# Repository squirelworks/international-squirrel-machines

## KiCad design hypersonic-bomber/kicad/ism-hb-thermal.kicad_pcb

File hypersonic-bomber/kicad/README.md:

# ISM Hypersonic Bomber — KiCad (thermal / TPS sense) (#37)

Study-scale **educational thermal / TPS instrumentation** board for ISM-HB-1. Open with **KiCad 8**.

## Out of scope (hard)

- **No** weapons, munitions, guidance, seekers, warheads, fuzing, or arming
- **No** operational employment or targeting
- **No** scramjet / propulsion design recipes
- **No** ITAR/EAR TPS formulations or classified materials data
- Channels are **teaching sense / status stubs** only

## Project-local libraries

| File | Role |
|------|------|
| `sym-lib-table` | `ISM.kicad_sym` |
| `fp-lib-table` | `ISM.pretty/` |
| `ISM.kicad_sym` / `ISM.pretty/` | Study MCU, IMU, RADIO, CONN |

## Schematic / PCB (`ism-hb-thermal`)

| Net / header | Role |
|--------------|------|
| I2C | IMU / cabin / skin sensors stub |
| SPI | Telemetry / flash stub |
| J1 `ADC_TC1` | Thermocouple / RTD sense stub |
| J2 `ADC_TC2` | Second thermal sense stub |
| J3 `GPIO_TPS_OK` | TPS health status stub |
| J4 `GPIO_OVERTEMP` | Over-temp inhibit packaging stub |
| 3V3 / 5V / GND | Rails with PWR_FLAG |

Study MCU footprint pitch is packaging-level (not production RP2040 0.4 mm).

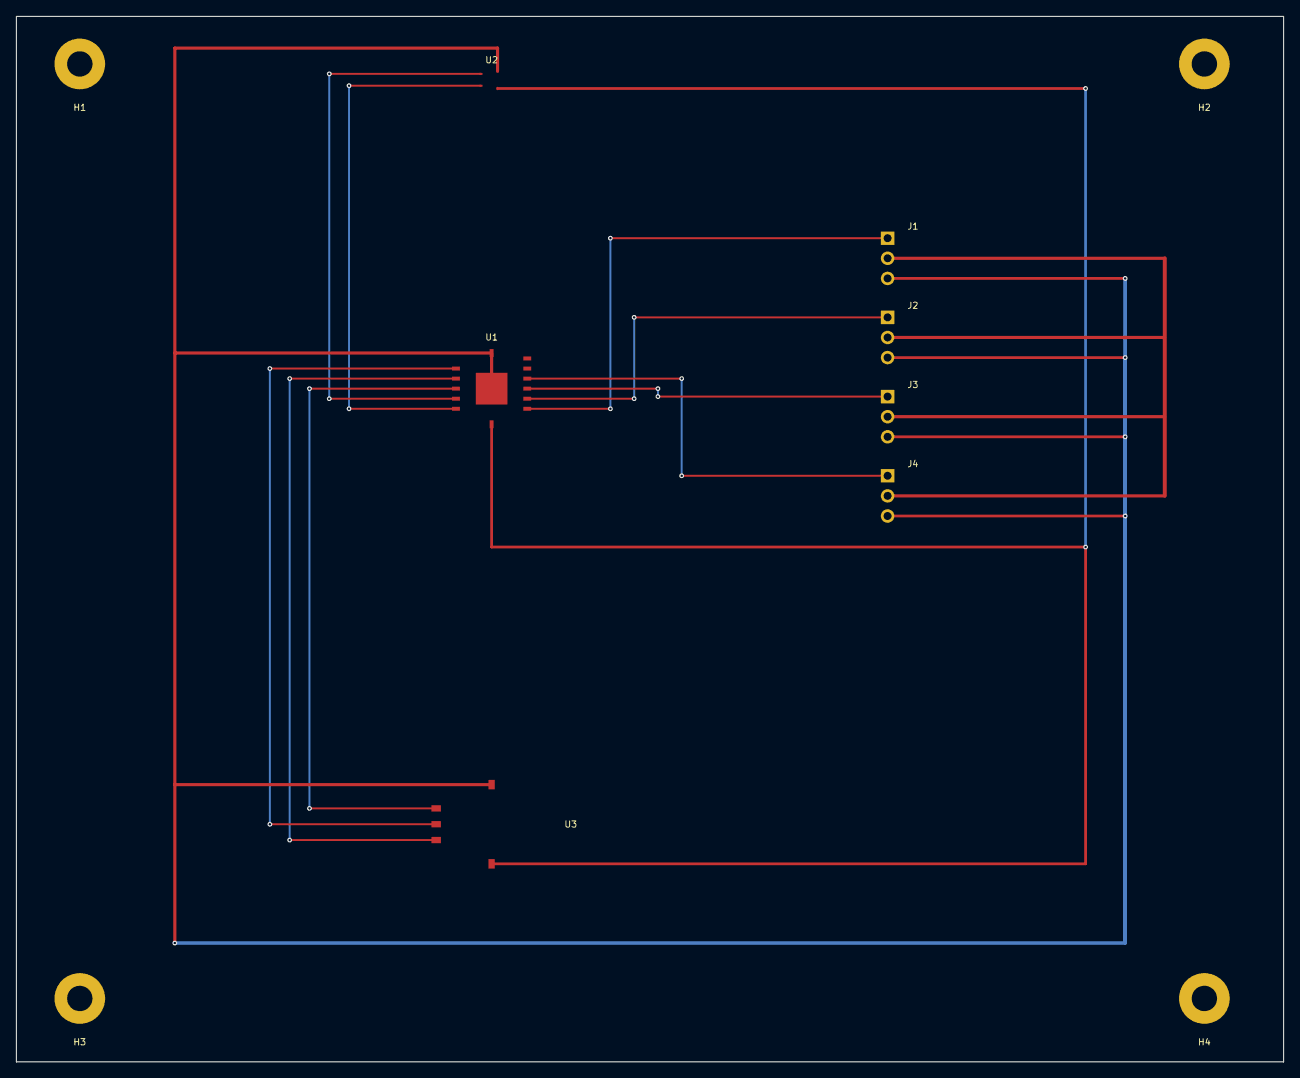
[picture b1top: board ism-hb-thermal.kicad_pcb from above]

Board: 2 copper layers, 160.0 x 132.0 mm, 11 parts (0 on the bottom side), 12 nets.

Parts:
H1, H2, H3, H4: M3; MountingHole_3.2mm_M3
J1: J1; PinHeader_1x03_P2.54mm
J2: J2; PinHeader_1x03_P2.54mm
J3: J3; PinHeader_1x03_P2.54mm
J4: J4; PinHeader_1x03_P2.54mm
U1: RP2040; QFN-56-1EP_7x7mm_P0.4mm
U2: IMU; LGA-14_3x2.5mm_P0.5mm
U3: RADIO; RADIO_Module

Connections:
3V3: U1.11, U2.4, U3.5
5V: J1.2, J2.2, J3.2, J4.2
ADC_TC1: J1.1, U1.6
ADC_TC2: J2.1, U1.7
GND: J1.3, J2.3, J3.3, J4.3, U1.10, U1.EP, U2.3, U3.4
GPIO_OVERTEMP: J4.1, U1.9
GPIO_TPS_OK: J3.1, U1.8
I2C_SCL: U1.2, U2.2
I2C_SDA: U1.1, U2.1
SPI_MISO: U1.5, U3.2
SPI_MOSI: U1.4, U3.1
SPI_SCK: U1.3, U3.3

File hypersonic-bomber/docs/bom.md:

# Hypersonic bomber — educational master BOM (#37)

**Product:** ISM-HB-1  
**Slice:** study BOM tying the thermal/TPS-sense fab package to the blunt-cone STL / structural stubs.

## Out of scope (hard)

- Weapons, munitions, guidance, seekers, warheads, fuzing, or arming
- Operational employment, targeting, or mission planning
- Scramjet / propulsion **design recipes** or performance prediction
- Export-controlled (ITAR/EAR) TPS formulations or classified materials data
- **Not** a procurement order — PNs freeze at inquire-for-release

## Board (SMT) — from `../fab/BOM.csv`

| Ref | Qty | Value | Role |
|-----|-----|-------|------|
| U1 | 1 | RP2040 | Thermal / TPS sense MCU stub |
| U2 | 1 | IMU | Attitude stub |
| U3 | 1 | RADIO | Telemetry stub |
| J1 | 1 | PinHeader 1×03 | TPS thermistor / TC sense stub |
| J2 | 1 | PinHeader 1×03 | Heat-flux sense stub |
| J3 | 1 | PinHeader 1×03 | TPS health / spare thermal stub |
| J4 | 1 | PinHeader 1×03 | Over-temp packaging stub |
| H1–H4 | 4 | M3 hole | Board mounting |

## Mechanical / study article

| ID | Qty | Item | Source |
|----|-----|------|--------|
| MECH-CONE-STL | 1 | `blunt_cone_study.stl` print (blunt cone + TPS shell ghosts) | `../mechanical/` |
| MECH-SCAD | 1 | `blunt_cone_study.scad` parametric source | `../shell/` |
| MECH-FAST-M3 | lot | M3 hardware for thermal board tray | study |
| MECH-TRAY | 1 | Thermal-board tray stub under TPS shell | `structural.yaml` |
| TPS-CLASS | ref | Textbook TPS class coupon placeholders | `heat-shield-tps.md` — open literature classes only |

## Electrical harness (study)

| ID | Qty | Item | Notes |
|----|-----|------|-------|
| HAR-TC1 | 1 | Sense lead | J1 teaching thermistor/TC stub |
| HAR-FLUX | 1 | Sense lead | J2 heat-flux stub |
| HAR-TPS | 1 | Status lead | J3 TPS_OK packaging stub |
| HAR-OT | 1 | Status lead | J4 over-temp packaging stub — not a weapon inhibit |
| HAR-PWR | 1 | 5 V / GND stub lead | Bench supply only |

## Out of BOM (explicit)

Weapons, seekers, guidance, munition propulsion, warheads, fuzing/arming, classified TPS recipes, scramjet design kits.

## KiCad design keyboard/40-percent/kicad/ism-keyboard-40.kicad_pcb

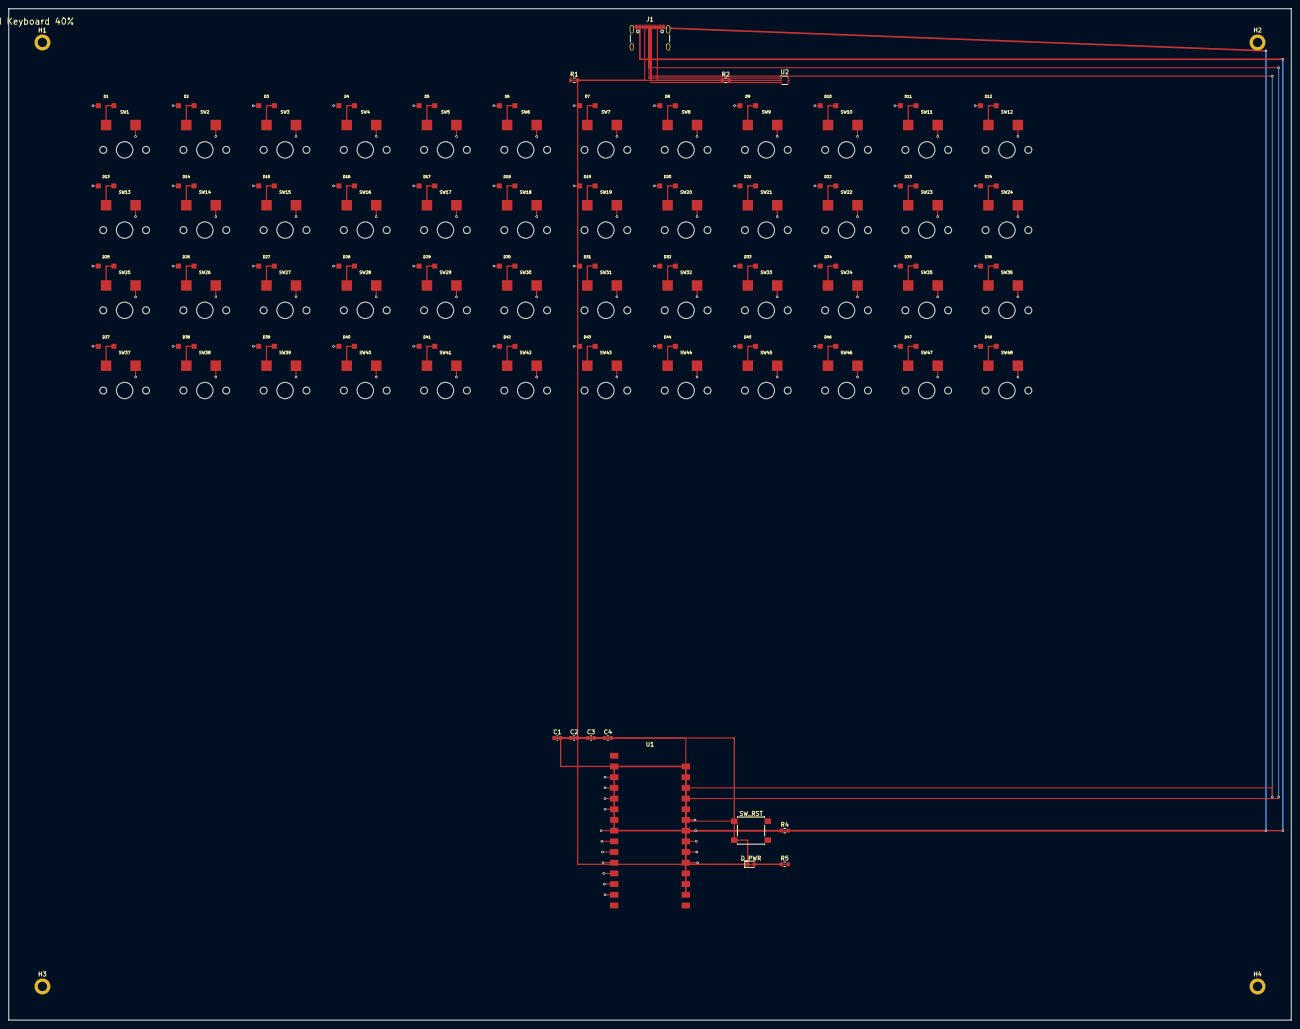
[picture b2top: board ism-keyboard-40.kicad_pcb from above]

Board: 4 copper layers, 304.6 x 240.2 mm, 113 parts (0 on the bottom side), 73 nets.

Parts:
C1, C2, C3, C4: 100nF; C_0603_1608Metric
D1, D2, D3, D4, D5, D6, D7, D8, D9, D10, D11, D12, D13, D14, D15, D16, D17, D18, D19, D20, D21, D22, D23, D24, D25, D26, D27, D28, D29, D30, D31, D32, D33, D34, D35, D36, D37, D38, D39, D40, D41, D42, D43, D44, D45, D46, D47, D48: 1N4148W; D_SOD123_nocrt
D_PWR: LED; LED_0603_1608Metric
H1, H2, H3, H4: M2; MountingHole_2.2mm_M2_DIN965_Pad
J1: USB_C; USB_C_Receptacle_GCT_USB4105-xx-A_16P_TopMnt_Horizontal
R1, R2: 5.1k; R_0603_1608Metric
R4: 10k; R_0603_1608Metric
R5: 1k; R_0603_1608Metric
SW1: ESC; SW_MX_Hotswap
SW2: Q; SW_MX_Hotswap
SW3: W; SW_MX_Hotswap
SW4: E; SW_MX_Hotswap
SW5: R; SW_MX_Hotswap
SW6: T; SW_MX_Hotswap
SW7: Y; SW_MX_Hotswap
SW8: U; SW_MX_Hotswap
SW9: I; SW_MX_Hotswap
SW10: O; SW_MX_Hotswap
SW11: P; SW_MX_Hotswap
SW12: BSPC; SW_MX_Hotswap
SW13: TAB; SW_MX_Hotswap
SW14: A; SW_MX_Hotswap
SW15: S; SW_MX_Hotswap
SW16: D; SW_MX_Hotswap
SW17: F; SW_MX_Hotswap
SW18: G; SW_MX_Hotswap
SW19: H; SW_MX_Hotswap
SW20: J; SW_MX_Hotswap
SW21: K; SW_MX_Hotswap
SW22: L; SW_MX_Hotswap
SW23: SCLN; SW_MX_Hotswap
SW24: ENT; SW_MX_Hotswap
SW25: LSFT; SW_MX_Hotswap
SW26: Z; SW_MX_Hotswap
SW27: X; SW_MX_Hotswap
SW28: C; SW_MX_Hotswap
SW29: V; SW_MX_Hotswap
SW30: B; SW_MX_Hotswap
SW31: N; SW_MX_Hotswap
SW32: M; SW_MX_Hotswap
SW33: COMM; SW_MX_Hotswap
SW34: DOT; SW_MX_Hotswap
SW35: SLSH; SW_MX_Hotswap
SW36: RSFT; SW_MX_Hotswap
SW37: LCTL; SW_MX_Hotswap
SW38: LGUI; SW_MX_Hotswap
SW39: LALT; SW_MX_Hotswap
SW40: FN; SW_MX_Hotswap
SW41: SPC; SW_MX_Hotswap
SW42: SPC2; SW_MX_Hotswap
SW43: SPC3; SW_MX_Hotswap
SW44: RALT; SW_MX_Hotswap
SW45: LEFT; SW_MX_Hotswap
SW46: DOWN; SW_MX_Hotswap
SW47: UP; SW_MX_Hotswap
SW48: RIGHT; SW_MX_Hotswap
SW_RST: RESET; SW_SPST_PTS645
U1: RP2040_MOD; ISM_RP2040_Module
U2: USBLC6-2SC6; SOT-666

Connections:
+3V3: C1.1, C2.1, C3.1, C4.1, R4.2, R5.1, U1.14
+5V: J1.A4, J1.A9, J1.B4, J1.B9, U1.15, U2.5
CC1: J1.A5, R1.1
CC2: J1.B5, R2.1
COL0: D1.1, D13.1, D25.1, D37.1, U1.7
COL1: D2.1, D14.1, D26.1, D38.1, U1.8
COL2: D3.1, D15.1, D27.1, D39.1, U1.9
COL3: D4.1, D16.1, D28.1, D40.1, U1.10
COL4: D5.1, D17.1, D29.1, D41.1, U1.11
COL5: D6.1, D18.1, D30.1, D42.1, U1.12
COL6: D7.1, D19.1, D31.1, D43.1, U1.13
COL7: D8.1, D20.1, D32.1, D44.1, U1.19
COL8: D9.1, D21.1, D33.1, D45.1, U1.20
COL9: D10.1, D22.1, D34.1, D46.1, U1.21
COL10: D11.1, D23.1, D35.1, D47.1, U1.22
COL11: D12.1, D24.1, D36.1, D48.1, U1.23
GND: C1.2, C2.2, C3.2, C4.2, D_PWR.1, J1.A1, J1.A8, J1.A12, J1.B1, J1.B8, J1.B12, J1.S1, R1.2, R2.2, SW_RST.2, U1.1, U1.26, U2.2
LED_A: D_PWR.2, R5.2
NET_SW1: D1.2, SW1.2
NET_SW2: D2.2, SW2.2
NET_SW3: D3.2, SW3.2
NET_SW4: D4.2, SW4.2
NET_SW5: D5.2, SW5.2
NET_SW6: D6.2, SW6.2
NET_SW7: D7.2, SW7.2
NET_SW8: D8.2, SW8.2
NET_SW9: D9.2, SW9.2
NET_SW10: D10.2, SW10.2
NET_SW11: D11.2, SW11.2
NET_SW12: D12.2, SW12.2
NET_SW13: D13.2, SW13.2
NET_SW14: D14.2, SW14.2
NET_SW15: D15.2, SW15.2
NET_SW16: D16.2, SW16.2
NET_SW17: D17.2, SW17.2
NET_SW18: D18.2, SW18.2
NET_SW19: D19.2, SW19.2
NET_SW20: D20.2, SW20.2
NET_SW21: D21.2, SW21.2
NET_SW22: D22.2, SW22.2
NET_SW23: D23.2, SW23.2
NET_SW24: D24.2, SW24.2
NET_SW25: D25.2, SW25.2
NET_SW26: D26.2, SW26.2
NET_SW27: D27.2, SW27.2
NET_SW28: D28.2, SW28.2
NET_SW29: D29.2, SW29.2
NET_SW30: D30.2, SW30.2
NET_SW31: D31.2, SW31.2
NET_SW32: D32.2, SW32.2
NET_SW33: D33.2, SW33.2
NET_SW34: D34.2, SW34.2
NET_SW35: D35.2, SW35.2
NET_SW36: D36.2, SW36.2
NET_SW37: D37.2, SW37.2
NET_SW38: D38.2, SW38.2
NET_SW39: D39.2, SW39.2
NET_SW40: D40.2, SW40.2
NET_SW41: D41.2, SW41.2
NET_SW42: D42.2, SW42.2
NET_SW43: D43.2, SW43.2
NET_SW44: D44.2, SW44.2
NET_SW45: D45.2, SW45.2
NET_SW46: D46.2, SW46.2
NET_SW47: D47.2, SW47.2
NET_SW48: D48.2, SW48.2
ROW0: SW1.1, SW2.1, SW3.1, SW4.1, SW5.1, SW6.1, SW7.1, SW8.1, SW9.1, SW10.1, SW11.1, SW12.1, U1.2
ROW1: SW13.1, SW14.1, SW15.1, SW16.1, SW17.1, SW18.1, SW19.1, SW20.1, SW21.1, SW22.1, SW23.1, SW24.1, U1.3
ROW2: SW25.1, SW26.1, SW27.1, SW28.1, SW29.1, SW30.1, SW31.1, SW32.1, SW33.1, SW34.1, SW35.1, SW36.1, U1.4
ROW3: SW37.1, SW38.1, SW39.1, SW40.1, SW41.1, SW42.1, SW43.1, SW44.1, SW45.1, SW46.1, SW47.1, SW48.1, U1.5
RUN: R4.1, SW_RST.1, U1.18
USB_DM: J1.A7, J1.B7, U1.16, U2.3, U2.4
USB_DP: J1.A6, J1.B6, U1.17, U2.1, U2.6

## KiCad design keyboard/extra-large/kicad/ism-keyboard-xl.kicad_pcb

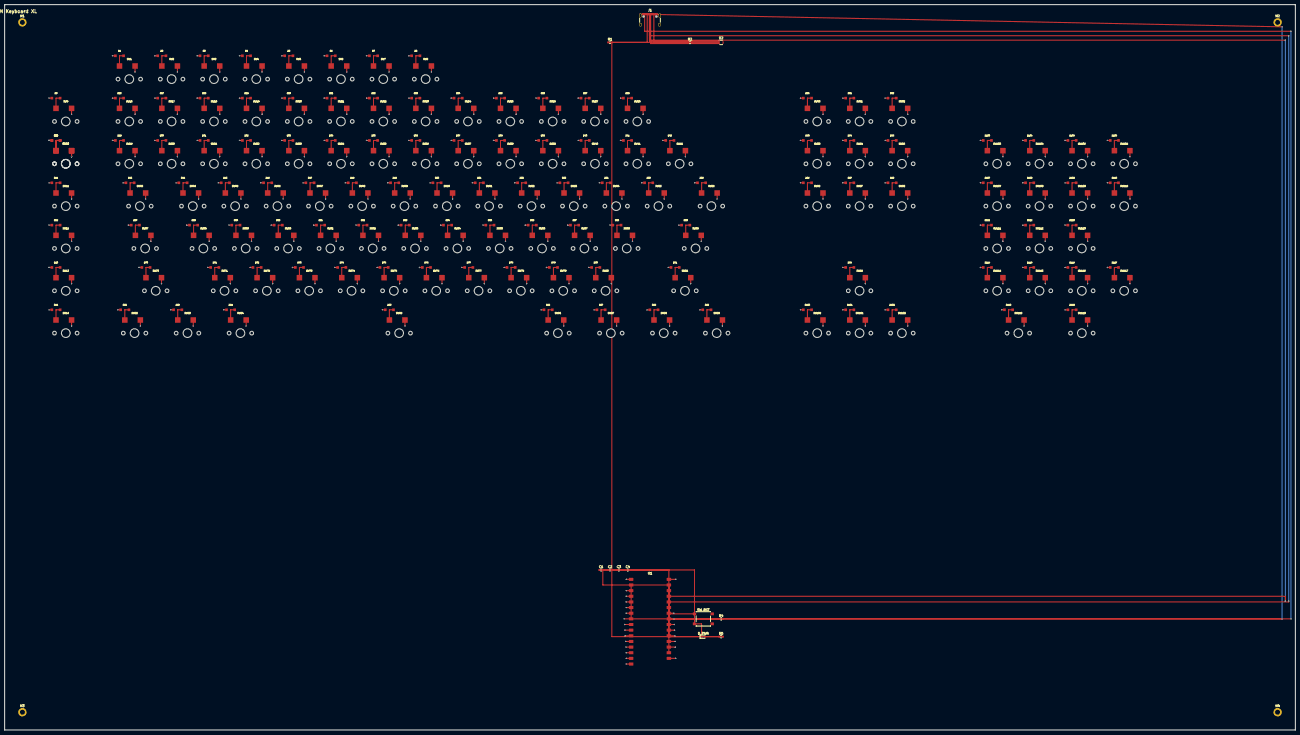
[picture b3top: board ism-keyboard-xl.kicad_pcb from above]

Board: 4 copper layers, 580.8 x 326.4 mm, 255 parts (0 on the bottom side), 152 nets.

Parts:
C1, C2, C3, C4: 100nF; C_0603_1608Metric
D1, D2, D3, D4, D5, D6, D7, D8, D9, D10, D11, D12, D13, D14, D15, D16, D17, D18, D19, D20, D21, D22, D23, D24, D25, D26, D27, D28, D29, D30, D31, D32, D33, D34, D35, D36, D37, D38, D39, D40, D41, D42, D43, D44, D45, D46, D47, D48, D49, D50, D51, D52, D53, D54, D55, D56, D57, D58, D59, D60, D61, D62, D63, D64, D65, D66, D67, D68, D69, D70, D71, D72, D73, D74, D75, D76, D77, D78, D79, D80, D81, D82, D83, D84, D85, D86, D87, D88, D89, D90, D91, D92, D93, D94, D95, D96, D97, D98, D99, D100, D101, D102, D103, D104, D105, D106, D107, D108, D109, D110, D111, D112, D113, D114, D115, D116, D117, D118, D119: 1N4148W; D_SOD123_nocrt
D_PWR: LED; LED_0603_1608Metric
H1, H2, H3, H4: M2; MountingHole_2.2mm_M2_DIN965_Pad
J1: USB_C; USB_C_Receptacle_GCT_USB4105-xx-A_16P_TopMnt_Horizontal
R1, R2: 5.1k; R_0603_1608Metric
R4: 10k; R_0603_1608Metric
R5: 1k; R_0603_1608Metric
SW1: VOLD; SW_MX_Hotswap
SW2: VOLU; SW_MX_Hotswap
SW3: MUTE; SW_MX_Hotswap
SW4: PREV; SW_MX_Hotswap
SW5: PLAY; SW_MX_Hotswap
SW6: NEXT; SW_MX_Hotswap
SW7: STOP; SW_MX_Hotswap
SW8: CALC; SW_MX_Hotswap
SW9: M1; SW_MX_Hotswap
SW10: M2; SW_MX_Hotswap
SW11: M3; SW_MX_Hotswap
SW12: M4; SW_MX_Hotswap
SW13: M5; SW_MX_Hotswap
SW14: M6; SW_MX_Hotswap
SW15: M7; SW_MX_Hotswap
SW16: ESC; SW_MX_Hotswap
SW17: F1; SW_MX_Hotswap
SW18: F2; SW_MX_Hotswap
SW19: F3; SW_MX_Hotswap
SW20: F4; SW_MX_Hotswap
SW21: F5; SW_MX_Hotswap
SW22: F6; SW_MX_Hotswap
SW23: F7; SW_MX_Hotswap
SW24: F8; SW_MX_Hotswap
SW25: F9; SW_MX_Hotswap
SW26: F10; SW_MX_Hotswap
SW27: F11; SW_MX_Hotswap
SW28: F12; SW_MX_Hotswap
SW29: GRV; SW_MX_Hotswap
SW30: 1; SW_MX_Hotswap
SW31: 2; SW_MX_Hotswap
SW32: 3; SW_MX_Hotswap
SW33: 4; SW_MX_Hotswap
SW34: 5; SW_MX_Hotswap
SW35: 6; SW_MX_Hotswap
SW36: 7; SW_MX_Hotswap
SW37: 8; SW_MX_Hotswap
SW38: 9; SW_MX_Hotswap
SW39: 0; SW_MX_Hotswap
SW40: MIN; SW_MX_Hotswap
SW41: EQL; SW_MX_Hotswap
SW42: BSPC; SW_MX_Hotswap
SW43: TAB; SW_MX_Hotswap
SW44: Q; SW_MX_Hotswap
SW45: W; SW_MX_Hotswap
SW46: E; SW_MX_Hotswap
SW47: R; SW_MX_Hotswap
SW48: T; SW_MX_Hotswap
SW49: Y; SW_MX_Hotswap
SW50: U; SW_MX_Hotswap
SW51: I; SW_MX_Hotswap
SW52: O; SW_MX_Hotswap
SW53: P; SW_MX_Hotswap
SW54: LBRC; SW_MX_Hotswap
SW55: RBRC; SW_MX_Hotswap
SW56: BSLS; SW_MX_Hotswap
SW57: CAPS; SW_MX_Hotswap
SW58: A; SW_MX_Hotswap
SW59: S; SW_MX_Hotswap
SW60: D; SW_MX_Hotswap
SW61: F; SW_MX_Hotswap
SW62: G; SW_MX_Hotswap
SW63: H; SW_MX_Hotswap
SW64: J; SW_MX_Hotswap
SW65: K; SW_MX_Hotswap
SW66: L; SW_MX_Hotswap
SW67: SCLN; SW_MX_Hotswap
SW68: QUOT; SW_MX_Hotswap
SW69: ENT; SW_MX_Hotswap
SW70: LSFT; SW_MX_Hotswap
SW71: Z; SW_MX_Hotswap
SW72: X; SW_MX_Hotswap
SW73: C; SW_MX_Hotswap
SW74: V; SW_MX_Hotswap
SW75: B; SW_MX_Hotswap
SW76: N; SW_MX_Hotswap
SW77: M; SW_MX_Hotswap
SW78: COMM; SW_MX_Hotswap
SW79: DOT; SW_MX_Hotswap
SW80: SLSH; SW_MX_Hotswap
SW81: RSFT; SW_MX_Hotswap
SW82: LCTL; SW_MX_Hotswap
SW83: LGUI; SW_MX_Hotswap
SW84: LALT; SW_MX_Hotswap
SW85: SPC; SW_MX_Hotswap
SW86: RALT; SW_MX_Hotswap
SW87: RGUI; SW_MX_Hotswap
SW88: MENU; SW_MX_Hotswap
SW89: RCTL; SW_MX_Hotswap
SW90: PRSC; SW_MX_Hotswap
SW91: SLCK; SW_MX_Hotswap
SW92: PAUSE; SW_MX_Hotswap
SW93: INS; SW_MX_Hotswap
SW94: HOME; SW_MX_Hotswap
SW95: PGUP; SW_MX_Hotswap
SW96: DEL; SW_MX_Hotswap
SW97: END; SW_MX_Hotswap
SW98: PGDN; SW_MX_Hotswap
SW99: UP; SW_MX_Hotswap
SW100: LEFT; SW_MX_Hotswap
SW101: DOWN; SW_MX_Hotswap
SW102: RIGHT; SW_MX_Hotswap
SW103: NUMLK; SW_MX_Hotswap
SW104: NPDIV; SW_MX_Hotswap
SW105: NPMUL; SW_MX_Hotswap
SW106: NPSUB; SW_MX_Hotswap
SW107: NP7; SW_MX_Hotswap
SW108: NP8; SW_MX_Hotswap
SW109: NP9; SW_MX_Hotswap
SW110: NPADD; SW_MX_Hotswap
SW111: NP4; SW_MX_Hotswap
SW112: NP5; SW_MX_Hotswap
SW113: NP6; SW_MX_Hotswap
SW114: NP1; SW_MX_Hotswap
SW115: NP2; SW_MX_Hotswap
SW116: NP3; SW_MX_Hotswap
SW117: NPENT; SW_MX_Hotswap
SW118: NP0; SW_MX_Hotswap
SW119: NPDOT; SW_MX_Hotswap
SW_RST: RESET; SW_SPST_PTS645
U1: RP2040_MOD; ISM_RP2040_Module
U2: USBLC6-2SC6; SOT-666

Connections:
+3V3: C1.1, C2.1, C3.1, C4.1, R4.2, R5.1, U1.14
+5V: J1.A4, J1.A9, J1.B4, J1.B9, U1.15, U2.5
CC1: J1.A5, R1.1
CC2: J1.B5, R2.1
COL0: D1.1, D16.1, D29.1, D43.1, D57.1, D70.1, D82.1, D103.1, U1.7
COL1: D2.1, D17.1, D30.1, D44.1, D58.1, D71.1, D83.1, D104.1, U1.8
COL2: D3.1, D18.1, D31.1, D45.1, D59.1, D72.1, D84.1, D105.1, U1.9
COL3: D4.1, D19.1, D32.1, D46.1, D60.1, D73.1, D85.1, D106.1, U1.10
COL4: D5.1, D20.1, D33.1, D47.1, D61.1, D74.1, D86.1, D107.1, U1.11
COL5: D6.1, D21.1, D34.1, D48.1, D62.1, D75.1, D87.1, D108.1, U1.12
COL6: D7.1, D22.1, D35.1, D49.1, D63.1, D76.1, D88.1, D109.1, U1.13
COL7: D8.1, D23.1, D36.1, D50.1, D64.1, D77.1, D89.1, D110.1, U1.19
COL8: D24.1, D37.1, D51.1, D65.1, D78.1, D92.1, D111.1, U1.20
COL9: D25.1, D38.1, D52.1, D66.1, D79.1, D100.1, D112.1, U1.21
COL10: D26.1, D39.1, D53.1, D67.1, D80.1, D101.1, D113.1, U1.22
COL11: D27.1, D40.1, D54.1, D68.1, D81.1, D102.1, D114.1, U1.23
COL12: D28.1, D41.1, D55.1, D69.1, D97.1, D115.1, D118.1, U1.24
COL13: D42.1, D56.1, D90.1, D94.1, D98.1, D116.1, D119.1, U1.25
COL14: D91.1, D93.1, D95.1, D96.1, D99.1, D117.1, U1.28
COL15: D9.1, D10.1, D11.1, D12.1, D13.1, D14.1, D15.1, U1.30
GND: C1.2, C2.2, C3.2, C4.2, D_PWR.1, J1.A1, J1.A8, J1.A12, J1.B1, J1.B8, J1.B12, J1.S1, R1.2, R2.2, SW_RST.2, U1.1, U1.26, U2.2
LED_A: D_PWR.2, R5.2
NET_SW1: D1.2, SW1.2
NET_SW2: D2.2, SW2.2
NET_SW3: D3.2, SW3.2
NET_SW4: D4.2, SW4.2
NET_SW5: D5.2, SW5.2
NET_SW6: D6.2, SW6.2
NET_SW7: D7.2, SW7.2
NET_SW8: D8.2, SW8.2
NET_SW9: D9.2, SW9.2
NET_SW10: D10.2, SW10.2
NET_SW11: D11.2, SW11.2
NET_SW12: D12.2, SW12.2
NET_SW13: D13.2, SW13.2
NET_SW14: D14.2, SW14.2
NET_SW15: D15.2, SW15.2
NET_SW16: D16.2, SW16.2
NET_SW17: D17.2, SW17.2
NET_SW18: D18.2, SW18.2
NET_SW19: D19.2, SW19.2
NET_SW20: D20.2, SW20.2
NET_SW21: D21.2, SW21.2
NET_SW22: D22.2, SW22.2
NET_SW23: D23.2, SW23.2
NET_SW24: D24.2, SW24.2
NET_SW25: D25.2, SW25.2
NET_SW26: D26.2, SW26.2
NET_SW27: D27.2, SW27.2
NET_SW28: D28.2, SW28.2
NET_SW29: D29.2, SW29.2
NET_SW30: D30.2, SW30.2
NET_SW31: D31.2, SW31.2
NET_SW32: D32.2, SW32.2
NET_SW33: D33.2, SW33.2
NET_SW34: D34.2, SW34.2
NET_SW35: D35.2, SW35.2
NET_SW36: D36.2, SW36.2
NET_SW37: D37.2, SW37.2
NET_SW38: D38.2, SW38.2
NET_SW39: D39.2, SW39.2
NET_SW40: D40.2, SW40.2
NET_SW41: D41.2, SW41.2
NET_SW42: D42.2, SW42.2
NET_SW43: D43.2, SW43.2
NET_SW44: D44.2, SW44.2
NET_SW45: D45.2, SW45.2
NET_SW46: D46.2, SW46.2
NET_SW47: D47.2, SW47.2
NET_SW48: D48.2, SW48.2
NET_SW49: D49.2, SW49.2
NET_SW50: D50.2, SW50.2
NET_SW51: D51.2, SW51.2
NET_SW52: D52.2, SW52.2
NET_SW53: D53.2, SW53.2
NET_SW54: D54.2, SW54.2
NET_SW55: D55.2, SW55.2
NET_SW56: D56.2, SW56.2
NET_SW57: D57.2, SW57.2
NET_SW58: D58.2, SW58.2
NET_SW59: D59.2, SW59.2
NET_SW60: D60.2, SW60.2
NET_SW61: D61.2, SW61.2
NET_SW62: D62.2, SW62.2
NET_SW63: D63.2, SW63.2
NET_SW64: D64.2, SW64.2
NET_SW65: D65.2, SW65.2
NET_SW66: D66.2, SW66.2
NET_SW67: D67.2, SW67.2
NET_SW68: D68.2, SW68.2
NET_SW69: D69.2, SW69.2
NET_SW70: D70.2, SW70.2
NET_SW71: D71.2, SW71.2
NET_SW72: D72.2, SW72.2
NET_SW73: D73.2, SW73.2
NET_SW74: D74.2, SW74.2
NET_SW75: D75.2, SW75.2
NET_SW76: D76.2, SW76.2
NET_SW77: D77.2, SW77.2
NET_SW78: D78.2, SW78.2
NET_SW79: D79.2, SW79.2
NET_SW80: D80.2, SW80.2
NET_SW81: D81.2, SW81.2
NET_SW82: D82.2, SW82.2
NET_SW83: D83.2, SW83.2
NET_SW84: D84.2, SW84.2
NET_SW85: D85.2, SW85.2
NET_SW86: D86.2, SW86.2
NET_SW87: D87.2, SW87.2
NET_SW88: D88.2, SW88.2
NET_SW89: D89.2, SW89.2
NET_SW90: D90.2, SW90.2
NET_SW91: D91.2, SW91.2
NET_SW92: D92.2, SW92.2
NET_SW93: D93.2, SW93.2
NET_SW94: D94.2, SW94.2
NET_SW95: D95.2, SW95.2
NET_SW96: D96.2, SW96.2
NET_SW97: D97.2, SW97.2
NET_SW98: D98.2, SW98.2
NET_SW99: D99.2, SW99.2
NET_SW100: D100.2, SW100.2
NET_SW101: D101.2, SW101.2
NET_SW102: D102.2, SW102.2
NET_SW103: D103.2, SW103.2
NET_SW104: D104.2, SW104.2
NET_SW105: D105.2, SW105.2
NET_SW106: D106.2, SW106.2
NET_SW107: D107.2, SW107.2
NET_SW108: D108.2, SW108.2
NET_SW109: D109.2, SW109.2
NET_SW110: D110.2, SW110.2
NET_SW111: D111.2, SW111.2
NET_SW112: D112.2, SW112.2
NET_SW113: D113.2, SW113.2
NET_SW114: D114.2, SW114.2
NET_SW115: D115.2, SW115.2
NET_SW116: D116.2, SW116.2
NET_SW117: D117.2, SW117.2
NET_SW118: D118.2, SW118.2
NET_SW119: D119.2, SW119.2
ROW0: SW9.1, SW16.1, SW17.1, SW18.1, SW19.1, SW20.1, SW21.1, SW22.1, SW23.1, SW24.1, SW25.1, SW26.1, SW27.1, SW28.1, SW90.1, SW91.1, U1.2
ROW1: SW10.1, SW29.1, SW30.1, SW31.1, SW32.1, SW33.1, SW34.1, SW35.1, SW36.1, SW37.1, SW38.1, SW39.1, SW40.1, SW41.1, SW42.1, SW93.1, U1.3
ROW2: SW11.1, SW43.1, SW44.1, SW45.1, SW46.1, SW47.1, SW48.1, SW49.1, SW50.1, SW51.1, SW52.1, SW53.1, SW54.1, SW55.1, SW56.1, SW96.1, U1.4
ROW3: SW12.1, SW57.1, SW58.1, SW59.1, SW60.1, SW61.1, SW62.1, SW63.1, SW64.1, SW65.1, SW66.1, SW67.1, SW68.1, SW69.1, SW94.1, SW95.1, U1.5
ROW4: SW13.1, SW70.1, SW71.1, SW72.1, SW73.1, SW74.1, SW75.1, SW76.1, SW77.1, SW78.1, SW79.1, SW80.1, SW81.1, SW97.1, SW98.1, SW99.1, U1.6
ROW5: SW14.1, SW82.1, SW83.1, SW84.1, SW85.1, SW86.1, SW87.1, SW88.1, SW89.1, SW92.1, SW100.1, SW101.1, SW102.1, SW118.1, SW119.1, U1.27
ROW6: SW15.1, SW103.1, SW104.1, SW105.1, SW106.1, SW107.1, SW108.1, SW109.1, SW110.1, SW111.1, SW112.1, SW113.1, SW114.1, SW115.1, SW116.1, SW117.1, U1.29
ROW7: SW1.1, SW2.1, SW3.1, SW4.1, SW5.1, SW6.1, SW7.1, SW8.1, U1.31
RUN: R4.1, SW_RST.1, U1.18
USB_DM: J1.A7, J1.B7, U1.16, U2.3, U2.4
USB_DP: J1.A6, J1.B6, U1.17, U2.1, U2.6
